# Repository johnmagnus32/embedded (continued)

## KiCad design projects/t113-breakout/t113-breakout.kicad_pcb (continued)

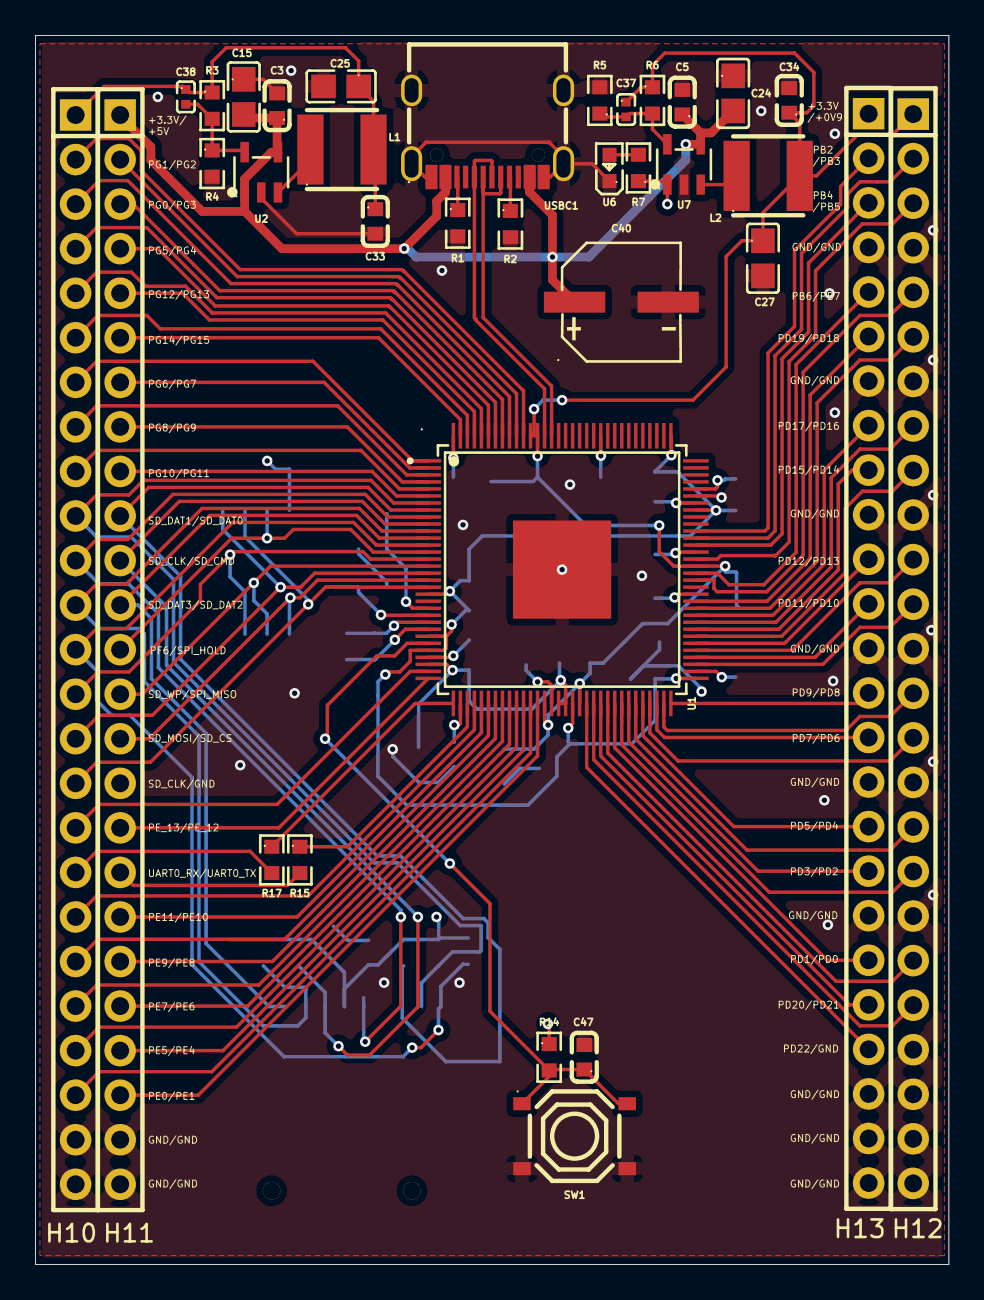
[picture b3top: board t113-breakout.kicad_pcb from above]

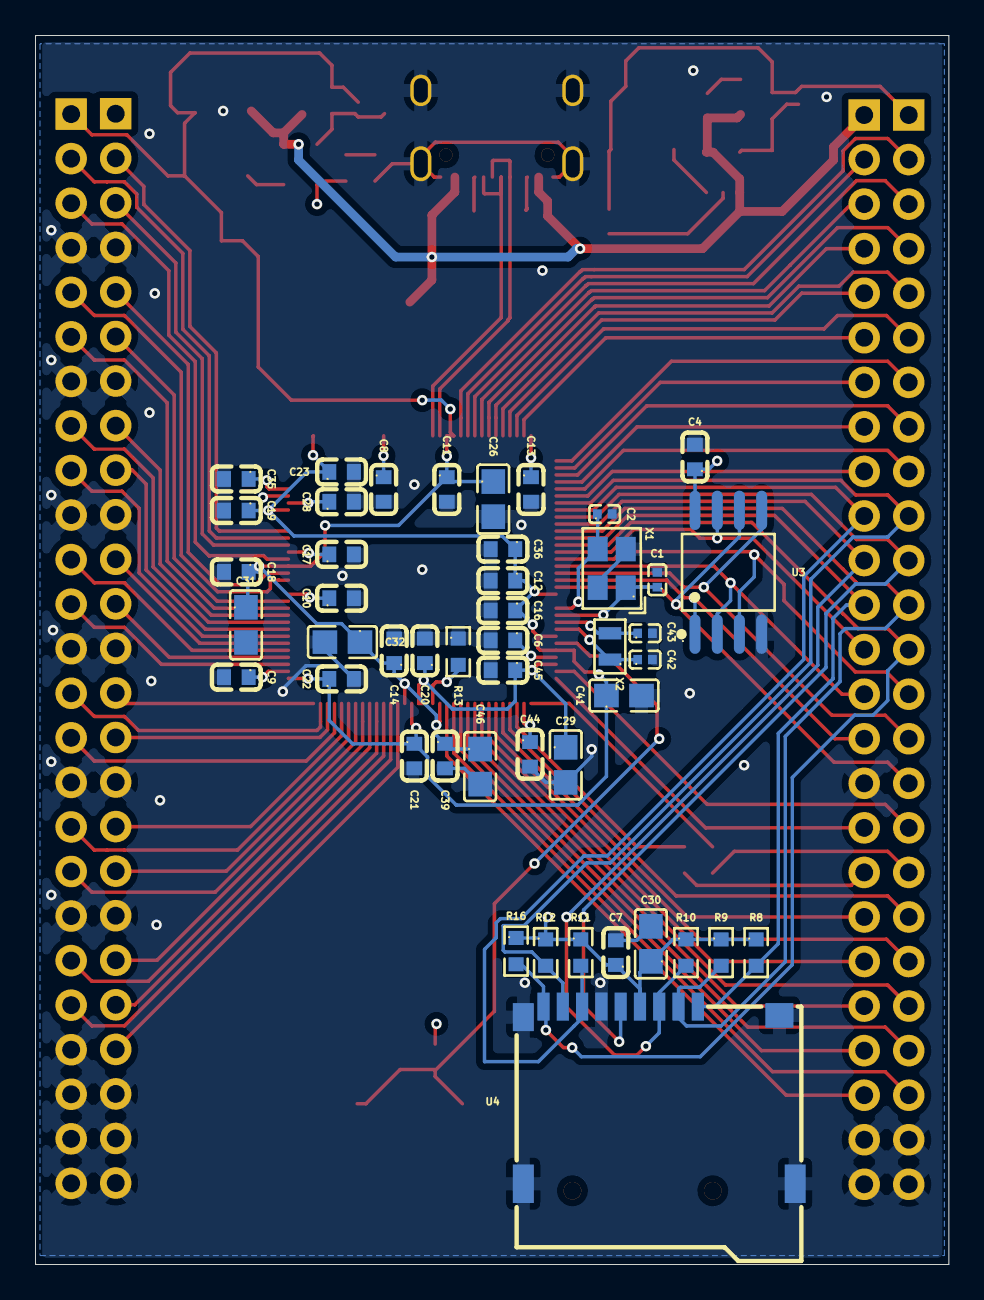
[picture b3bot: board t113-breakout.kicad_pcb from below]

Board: 4 copper layers, 52.1 x 70.1 mm, 80 parts (46 on the bottom side), 97 nets.

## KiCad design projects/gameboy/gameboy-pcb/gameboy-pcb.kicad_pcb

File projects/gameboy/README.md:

# Gameboy — STM32F411RE Jump Game

A side-scrolling jump game running on the STM32F411RE with an ILI9341 display, I2S audio, and button input.

## Pin Assignments (Nucleo-F411RE)

| Pin | Function | Peripheral | Notes |
|-----|----------|-----------|-------|
| PA4 | CS | SPI1 / ILI9341 Display | |
| PA5 | SCK | SPI1 / ILI9341 Display | |
| PA6 | MISO | SPI1 / ILI9341 Display | |
| PA7 | MOSI | SPI1 / ILI9341 Display | |
| PA9 | TX | USART1 (Debug UART) | |
| PA10 | RX | USART1 (Flash upload) | |
| PB0 | CS | W25Q128 Flash | |
| PB5 | DC | ILI9341 Display | |
| PC0 | Button A | Jump | |
| PC1 | Button B | SFX | |
| PC2 | Button Left | — | |
| PC3 | Button Right | — | |
| PC4 | Button Up | — | |
| PC5 | Button Down | — | |
| PC6 | Button Start | — | |
| PC7 | Button Select | — | |
| PB12 | WS (LRCK) | I2S2 (Audio) | |
| PB13 | SCK | I2S2 (Audio) | |
| PB15 | SD | I2S2 (Audio) | |
| PC10 | SCK | SPI3 (Flash) | Morpho header only |
| PC11 | MISO | SPI3 (Flash) | Morpho header only |
| PC12 | MOSI | SPI3 (Flash) | Morpho header only |

**Avoided pins:** PB8/PB9 have I2C pull-ups, PB12 is I2S2_WS on the Nucleo board — not suitable for pull-down buttons.

## ILI9341 Display Wiring

| Display Pin | Connect To |
|-------------|-----------|
| VIN | 5V |
| GND | GND |
| CS | PA4 |
| RESET | 3.3V (tied high) |
| DC | PB5 |
| MOSI (SDA) | PA7 |
| SCK | PA5 |
| LED (LITE) | 3.3V |
| MISO | PA6 |

**Important:** Solder bridge IM1, IM2, IM3 on the back of the display breakout for SPI mode. IM0 stays open.

## Buttons

Buttons connect between the GPIO pin and **3.3V**. Internal pull-down is enabled; rising edge (press down) triggers the interrupt.

| Button | Pin | Function |
|--------|-----|----------|
| A | PC0 | Jump |
| B | PC1 | SFX |
| Left | PC2 | — |
| Right | PC3 | — |
| Up | PC4 | — |
| Down | PC5 | — |
| Start | PC6 | — |
| Select | PC7 | — |

## UART Debug

115200 baud on PA9 (USART1 TX). Connect to a USB-UART adapter's RX pin.

## SPI Clock

SPI1 runs at 8 MHz (APB2 16 MHz / 2 prescaler). ILI9341 max is 10 MHz.

## Building

```bash
make
```

## Flashing (via ST-Link V2 + OpenOCD)

```bash
openocd -f interface/stlink-v2.cfg -f target/stm32f4x.cfg \
  -c "program build/gameboy.elf verify reset exit"
```

## Running in Simulator

```bash
cd ../../sim/mcu
./sim ../../projects/gameboy/build/gameboy.elf ../../projects/gameboy/build/songs.bin
```

Open http://localhost:3000 in a browser.

## Audio

Background music streams from the W25Q128 external flash over SPI3. The jump sound effect is synthesized in firmware.

### Converting audio

Place a WAV file at `assets/music.wav` and run:

```bash
make audio    # → build/songs.bin (8-bit unsigned PCM, 22050 Hz mono)
```

### Programming audio to flash

The firmware includes an upload mode triggered over UART. Requires `pyserial`:

```bash
pip install pyserial
python3 tools/flash_upload.py /dev/ttyUSB0 build/songs.bin
```

This takes ~5 minutes at 115200 baud for a 2.6MB file. The tool:
1. Sends `FLASH\n` to trigger upload mode
2. Firmware stops audio and responds `READY\n`
3. Tool sends 4-byte size + data in 256-byte pages
4. Firmware erases sectors and programs pages
5. Firmware reboots when done

### W25Q128 Flash Wiring

| Flash Pin | Connect To |
|-----------|-----------|
| CLK | PC10 (SPI3 SCK) |
| DI (MOSI) | PC12 (SPI3 MOSI) |
| DO (MISO) | PC11 (SPI3 MISO) |
| /CS | PB0 |
| VCC | 3.3V |
| /HOLD | 3.3V |
| /WP | 3.3V |
| GND | GND |

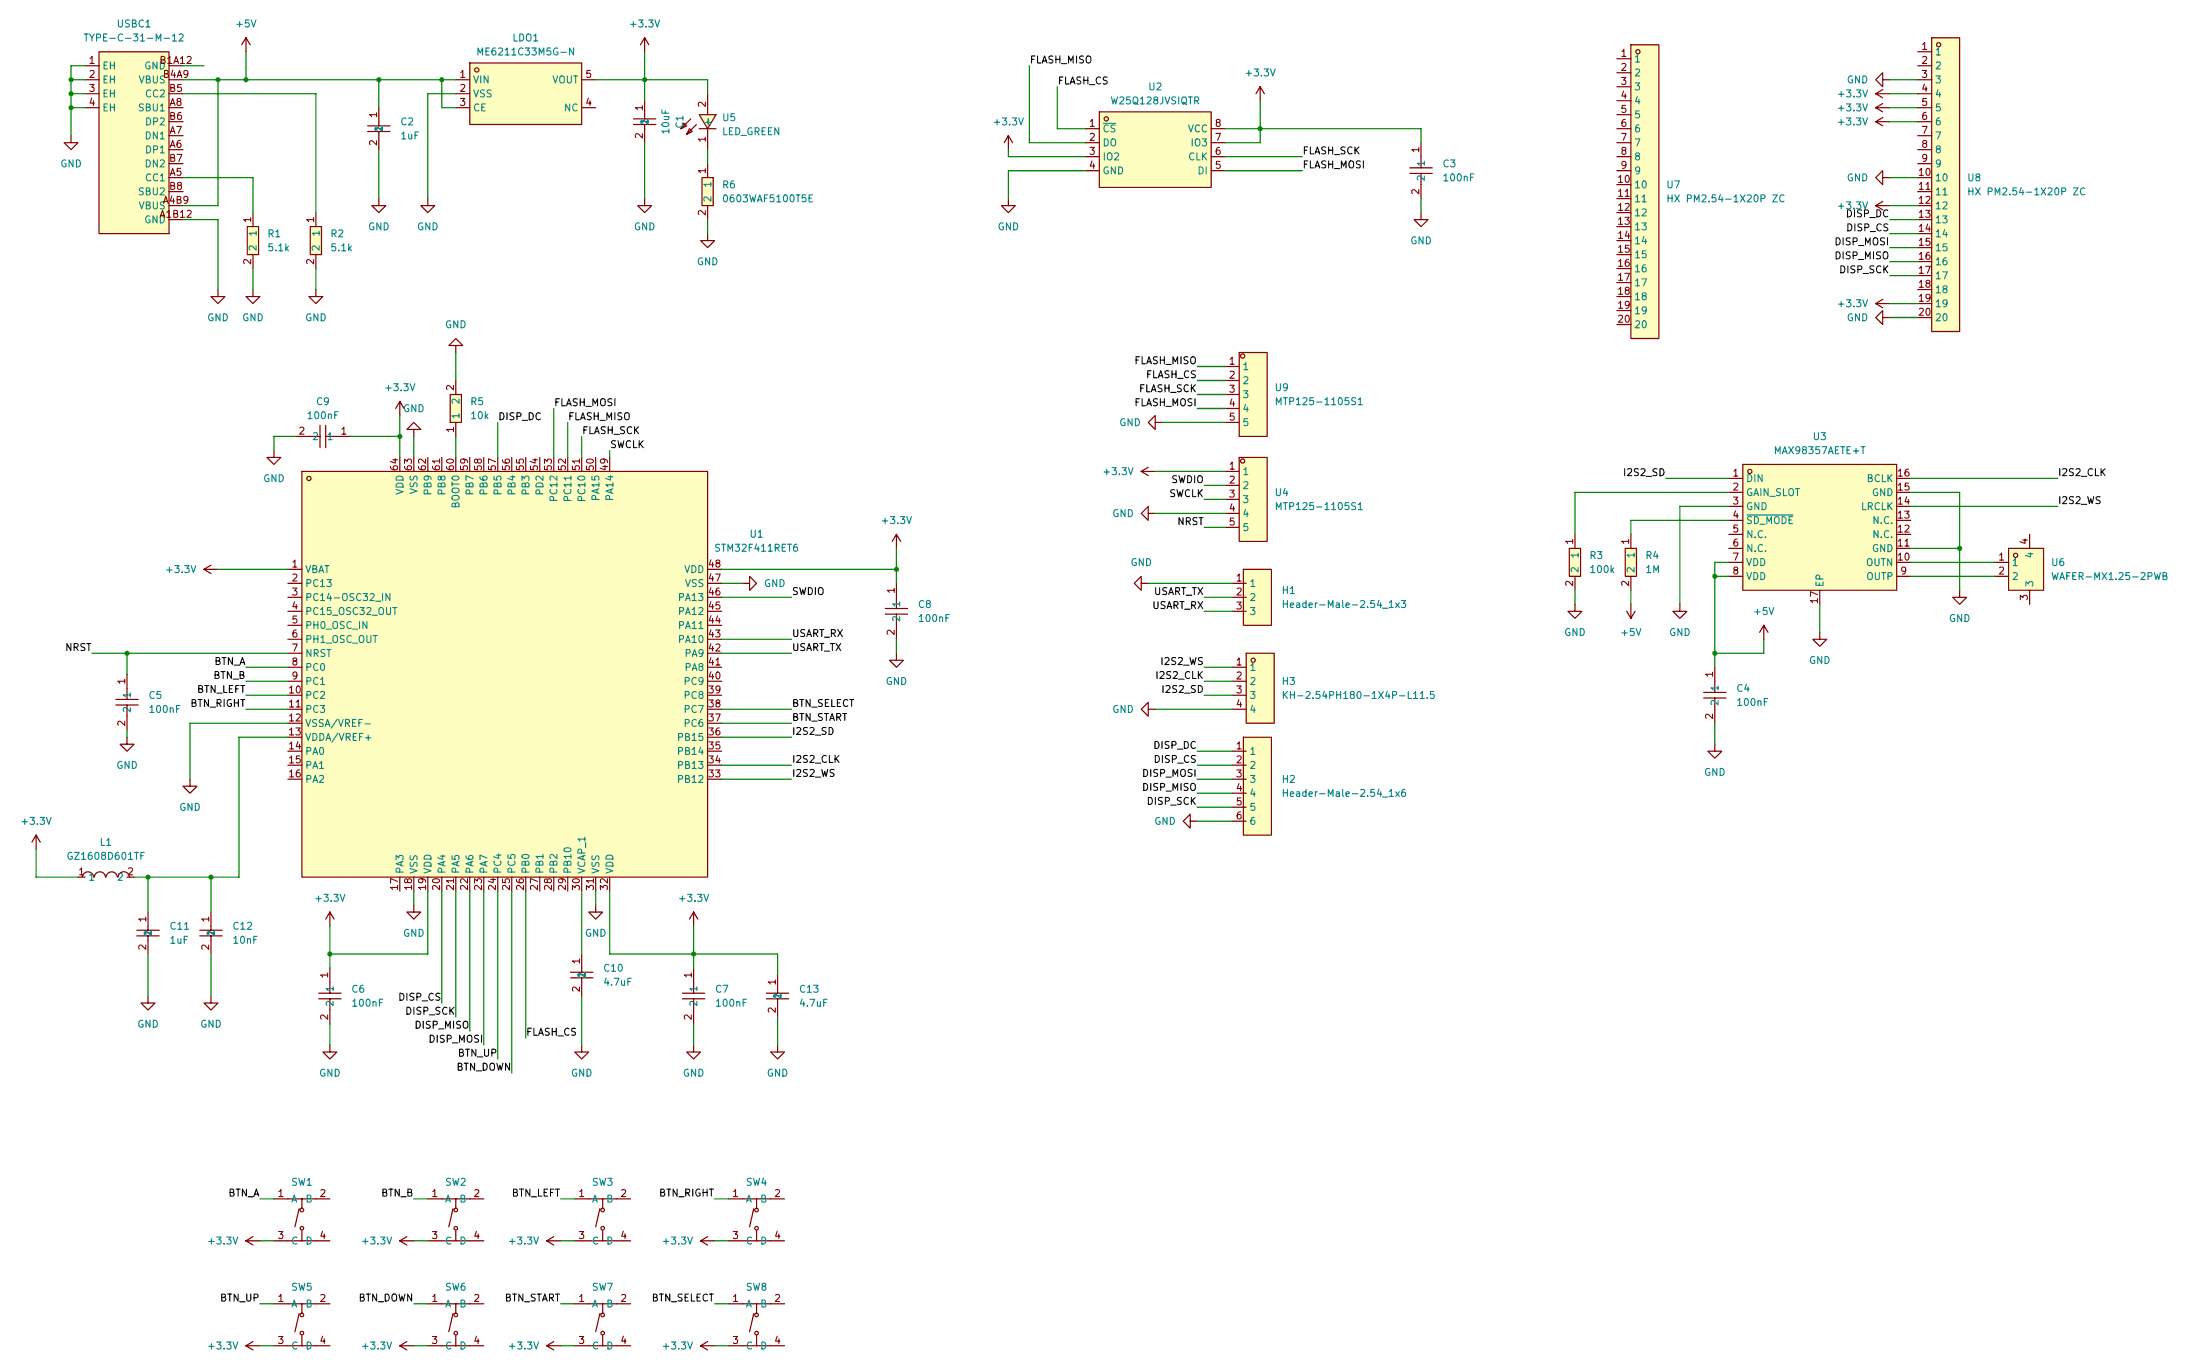
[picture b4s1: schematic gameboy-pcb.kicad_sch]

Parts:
C1: 10uF; C0805; MPN CL21A106KPFNNNE; LCSC Part C17024
C2, C11: 1uF; C0603; MPN CC0603KRX5R7BB105; LCSC Part C106215
C3, C4, C5, C6, C7, C8, C9: 100nF; C0603; MPN CC0603KRX7R9BB104; LCSC Part C14663
C10, C13: 4.7uF; C0603; MPN CC0603KRX5R6BB475; LCSC Part C109456
C12: 10nF; C0603; MPN CC0603KRX7R9BB103; LCSC Part C100042
H1: Header-Male-2.54_1x3; HDR-TH_3P-P2.54-V-M-1; MPN 2.54-1*3P针; LCSC Part C49257
H2: Header-Male-2.54_1x6; HDR-TH_6P-P2.54-V-M-1; MPN 2.54-1x6P直针; LCSC Part C37208
H3: KH-2.54PH180-1X4P-L11.5; HDR-TH_4P-P2.54-V-M; MPN KH-2.54PH180-1X4P-L11.5; LCSC Part C2905435
L1: GZ1608D601TF; L0603; MPN GZ1608D601TF; LCSC Part C1002
LDO1: ME6211C33M5G-N; SOT-23-5_L3.0-W1.7-P0.95-LS2.8-BL; MPN ME6211C33M5G-N; LCSC Part C82942
R1, R2: 5.1k; R0603; MPN RC0603FR-075K1L; LCSC Part C105580
R3: 100k; R0603; MPN RC0603FR-07100KL; LCSC Part C14675
R4: 1M; R0603; MPN RC0603FR-071ML; LCSC Part C105578
R5: 10k; R0603; MPN RC0603JR-0710KL; LCSC Part C99198
R6: 0603WAF5100T5E; R0603; MPN 0603WAF5100T5E; LCSC Part C23193
SW1, SW2, SW3, SW4, SW5, SW6, SW7, SW8: SW-SMD_4P-L5.1-W5.1-P3.70-LS6.5-TL_H1.5; MPN TS-1187A-B-A-B; LCSC Part C318884
U1: STM32F411RET6; LQFP-64_L10.0-W10.0-P0.50-LS12.0-BL; MPN STM32F411RET6; LCSC Part C94355
U2: W25Q128JVSIQTR; SOIC-8_L5.3-W5.3-P1.27-LS8.0-BL; MPN W25Q128JVSIQ; LCSC Part C97521
U3: MAX98357AETE+T; TQFN-16_L3.0-W3.0-P0.50-BL-EP1.5; MPN MAX98357AETE+T; LCSC Part C910544
U4, U9: MTP125-1105S1; HDR-TH_5P-P2.54-V-M; MPN MTP125-1105S1; LCSC Part C358687
U5: LED_GREEN; LED0603-RD; MPN 19-213SYGC/S530-E2/5T; LCSC Part C2986027
U6: WAFER-MX1.25-2PWB; CONN-SMD_2P-P1.25_XUNPU_WAFER-MX1.25-2PWB; MPN WAFER-MX1.25-2PWB; LCSC Part C3029359
U7, U8: HX PM2.54-1X20P ZC; HDR-TH_20P-P2.54-V-F; MPN HX PM2.54-1x20P ZC; LCSC Part C41417332
USBC1: TYPE-C-31-M-12; USB-C_SMD-TYPE-C-31-M-12_1; MPN TYPE-C-31-M-12; LCSC Part C165948

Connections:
+3.3V: C1.1, C3.1, C6.1, C7.1, C8.1, C9.1, C13.1, L1.1, LDO1.5 (VOUT), SW1.3 (C), SW2.3 (C), SW3.3 (C), SW4.3 (C), SW5.3 (C), SW6.3 (C), SW7.3 (C), SW8.3 (C), U1.1 (VBAT), U1.19 (VDD), U1.32 (VDD), U1.48 (VDD), U1.64 (VDD), U2.3 (IO2), U2.7 (IO3), U2.8 (VCC), U4.1, U5.2 (+), U8.4, U8.5, U8.6, U8.12, U8.19
+5V: C2.1, C4.1, LDO1.1 (VIN), LDO1.3 (CE), R4.2, U3.7 (VDD), U3.8 (VDD), USBC1.A4B9 (VBUS), USBC1.B4A9 (VBUS)
/BTN_A: SW1.1 (A), U1.8 (PC0)
/BTN_B: SW2.1 (A), U1.9 (PC1)
/BTN_DOWN: SW6.1 (A), U1.25 (PC5)
/BTN_LEFT: SW3.1 (A), U1.10 (PC2)
/BTN_RIGHT: SW4.1 (A), U1.11 (PC3)
/BTN_SELECT: SW8.1 (A), U1.38 (PC7)
/BTN_START: SW7.1 (A), U1.37 (PC6)
/BTN_UP: SW5.1 (A), U1.24 (PC4)
/DISP_CS: H2.2, U1.20 (PA4), U8.14
/DISP_DC: H2.1, U1.57 (PB5), U8.13
/DISP_MISO: H2.4, U1.22 (PA6), U8.16
/DISP_MOSI: H2.3, U1.23 (PA7), U8.15
/DISP_SCK: H2.5, U1.21 (PA5), U8.17
/FLASH_CS: U1.26 (PB0), U2.1 (~CS), U9.2
/FLASH_MISO: U1.52 (PC11), U2.2 (DO), U9.1
/FLASH_MOSI: U1.53 (PC12), U2.5 (DI), U9.4
/FLASH_SCK: U1.51 (PC10), U2.6 (CLK), U9.3
/I2S2_CLK: H3.2, U1.34 (PB13), U3.16 (BCLK)
/I2S2_SD: H3.3, U1.36 (PB15), U3.1 (DIN)
/I2S2_WS: H3.1, U1.33 (PB12), U3.14 (LRCLK)
/NRST: C5.1, U1.7 (NRST), U4.5
/SWCLK: U1.49 (PA14), U4.3
/SWDIO: U1.46 (PA13), U4.2
/USART_RX: H1.3, U1.43 (PA10)
/USART_TX: H1.2, U1.42 (PA9)
GND: C1.2, C2.2, C3.2, C4.2, C5.2, C6.2, C7.2, C8.2, C9.2, C10.2, C11.2, C12.2, C13.2, H1.1, H2.6, H3.4, LDO1.2 (VSS), R1.2, R2.2, R3.2, R5.2, R6.2, U1.12 (VSSA/VREF-), U1.18 (VSS), U1.31 (VSS), U1.47 (VSS), U1.63 (VSS), U2.4 (GND), U3.3 (GND), U3.11 (GND), U3.15 (GND), U3.17 (EP), U4.4, U8.3, U8.10, U8.20, U9.5, USBC1.1 (EH), USBC1.2 (EH), USBC1.3 (EH), USBC1.4 (EH), USBC1.A1B12 (GND)
unnamed: R5.1, U1.60 (BOOT0)
unnamed: C10.1, U1.30 (VCAP_1)
unnamed: C11.1, C12.1, L1.2, U1.13 (VDDA/VREF+)
unnamed: R3.1, U3.2 (GAIN_SLOT)
unnamed: U3.10 (OUTN), U6.1
unnamed: U3.9 (OUTP), U6.2
unnamed: R4.1, U3.4 (~SD_MODE)
unnamed: R6.1, U5.1 (-)
unnamed: R1.1, USBC1.A5 (CC1)
unnamed: R2.1, USBC1.B5 (CC2)

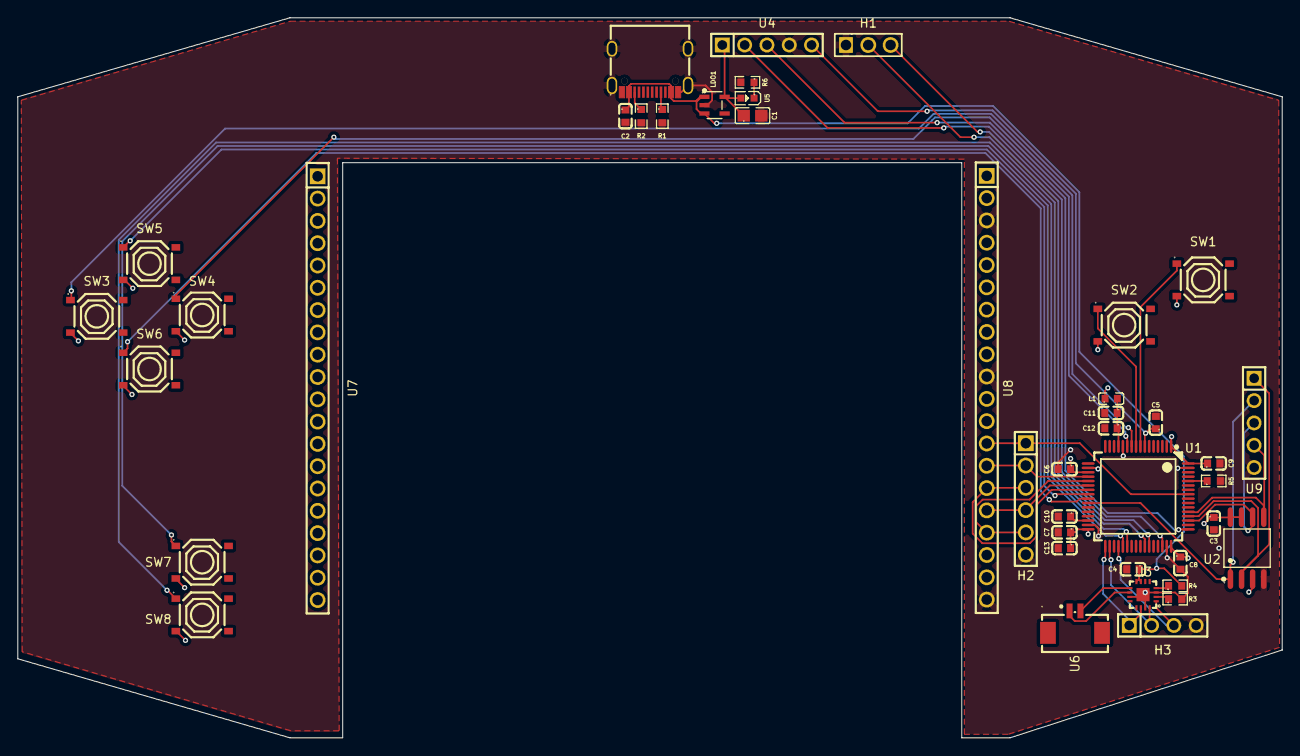
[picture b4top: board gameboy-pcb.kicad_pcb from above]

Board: 4 copper layers, 144.0 x 82.0 mm, 42 parts (0 on the bottom side), 38 nets.

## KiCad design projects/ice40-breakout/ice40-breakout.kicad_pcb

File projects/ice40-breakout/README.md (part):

# Breadboard iCE40UP5K Board (`ice40-breakout`)

**Status:** **Design complete** — schematic (`ice40-breakout.kicad_sch`), PCB
(`ice40-breakout.kicad_pcb`), and JLCPCB production files (`production/`) all live in this
directory. **Not yet fabricated / brought up.** Parts confirmed JLC-sourceable (see `BOM.md`).
**Audience:** Anyone (or a future Claude session) who needs to understand *why* this board exists,
*what it must do*, and *how it was built*. This file is the design rationale + spec; `BOM.md` holds
the as-built bill of materials and the full header pin map.

> **Provenance / how to read the code references.** This board serves a companion firmware project,
> `gameboy-v2`, which at the time of writing lives in `projects/gameboy-v2/` but is **not yet committed
> to git — it is an untracked/uncommitted work tree**. If you are reading this on a clean checkout (or
> a different worktree), those files **will not be present**, and that is expected — do not conclude the
> project "doesn't exist." This document is **self-contained**: every pin assignment, the configuration
> sequence, and the electrical spec are stated inline here and do not require opening any other file to
> trust them. The `projects/gameboy-v2/...` paths are given only so that, *if* you do have that work
> tree, you can cross-check against the source. The facts below are the authority; the file paths are a
> convenience.

> **As-built vs. spec.** Sections 1–3 and 5 were written as *requirements* before layout and remain the
> design rationale. The board has since been **built to this spec** — where a concrete build decision
> differs from or resolves an open question in the text, an **`[AS-BUILT]`** note points at the real
> value. The single authority for the final pinout is **`BOM.md`** (regenerated from
> `production/netlist.ipc`); this document is the *why*, `BOM.md` is the *what*.

---

## 0. In one paragraph

This is a custom breakout board for the **Lattice iCE40UP5K FPGA** (part `iCE40UP5K-SG48I`, the 48-pin
QFN package). In our system the FPGA is used as a graphics coprocessor (a "PPU") and is **configured
by an STM32 microcontroller over SPI at every power-up** — the STM32 streams the FPGA's bitstream in
on boot; there is no configuration flash on the FPGA side. Off-the-shelf iCE40 breakout boards
(iCEBreaker, UPduino) **cannot** be used for this, because they each carry an onboard SPI
configuration flash and a USB programmer wired onto the same SPI bus the STM32 needs to drive —
they contend on that bus and force the FPGA into self-boot ("master") mode. This board therefore
strips all of that out: it exposes just the FPGA, its power, and its config + I/O pins, so an external
STM32 is the sole controller of the configuration bus. Details below.

---

## 1. Why this board exists

### The product: gameboy-v2

`projects/gameboy-v2` is a handheld game console built from **two chips**:

- **STM32F411RE** (ARM Cortex-M4) — runs the game logic, audio, and input. Acts as the "CPU."
- **iCE40UP5K** (Lattice FPGA) — a **Picture Processing Unit (PPU)**. It renders sprites to an
  ILI9341 LCD autonomously. The STM32 sends sprite positions over SPI each frame; the FPGA does all
  pixel work and drives the display.

The defining architectural decision of gameboy-v2: **the STM32 configures the FPGA at every boot.**
The FPGA bitstream is *embedded in the STM32's firmware flash* and streamed into the FPGA over SPI on
power-up. There is **no FPGA-side configuration flash** in the product. (In the firmware this is a
function `fpga_load_bitstream()` that runs first thing in `main()`, before the game starts — the exact
sequence it performs is reproduced in section 2 below, so you do not need the source to follow it.)

Why do it this way? The iCE40 is **SRAM-based**: its logic configuration lives in volatile on-chip
SRAM that is wiped on every power loss. Something must reload it each boot. The gameboy-v2 chooses to
make the STM32 that "something" — one firmware image contains both the CPU program and the FPGA
bitstream, one flash operation programs the whole system, and there is no second flash chip to stock,
place, or program.

### The problem: dev boards don't work this way

The obvious way to prototype is to buy an off-the-shelf iCE40 dev board (iCEBreaker, UPduino) and wire
it to a Nucleo. **This does not faithfully reproduce the gameboy-v2 boot path**, for a concrete
electrical reason:

- Those boards are designed to **self-boot from an onboard SPI config flash** (iCE40 "master mode").
  They also carry an FTDI USB chip that programs that flash.
- Both the flash and the FTDI are wired **onto the FPGA's configuration SPI bus**. The config
  chip-select line (`SPI_SS_B`) is *the same net* as the flash's chip-select.
- If an external STM32 tries to slave-configure the FPGA, it must drive `SPI_SS_B` low — which also
  selects the onboard flash, causing **bus contention** on the shared data line. (This is the same
  reason `iceprog --help` notes that an iCEstick needs its flash chip desoldered for direct SRAM
  programming.)

So on a stock dev board you cannot cleanly let the STM32 own the config bus without physically
removing the flash. That is fragile and not representative.

### What this board is

A **minimal iCE40UP5K breakout with no onboard config flash and no USB programmer** — just the FPGA,
its power, decoupling, and headers. The STM32 is the *only* master of the config bus. This lets us:

1. Run the **exact, unmodified gameboy-v2 firmware** (`fpga_load_bitstream()` and all runtime code)
   on a breadboard, with the STM32 configuring the FPGA at boot — bit-for-bit like the final product.
2. Validate the real boot path, SPI protocol, PPU rendering, and LCD output on real silicon before
   committing to the integrated gameboy-v2 PCB.
3. Iterate on hardware cheaply (a ~15-component 2-layer board) with the risky/expensive integration
   (STM32 + FPGA + flash + LCD + audio on one board) deferred until the fundamentals are proven.

**Non-goal:** This board is *not* meant to self-boot or be programmed over USB. It has no persistence
of its own. If it has no STM32 driving it, it does nothing — exactly like the FPGA in the final
product.

---

## 2. The boot / configuration model (must be reproduced exactly)

The board's whole reason for existing is to reproduce this sequence, so it is spelled out in full here
(you do not need any other file to implement it). This is the **iCE40 SPI-slave configuration**
procedure (Lattice TN1248); the gameboy-v2 firmware implements it in `src/fpga_loader.c` — a function
named `fpga_load_bitstream()` called from `main()` before the game starts — but that file is in the
uncommitted work tree, so the canonical description is the numbered steps below:

```
1. CRESET_B  -> low     Clear configuration SRAM.
2. SPI_SS_B  -> low     Select SPI SLAVE config mode (this level is sampled when CRESET releases).
3. (hold ~1 us)
4. CRESET_B  -> high    Release reset. FPGA clears CRAM, then waits for the bitstream.
5. (wait ~1200 us)      Give the chip time to clear config memory before clocking data.
6. Clock the bitstream on MOSI, SPI mode 0 (CPOL=0, CPHA=0), MSB first.
7. Send >=49 trailing dummy clocks (firmware sends 7 bytes = 56 clocks) to finish wake-up.
8. SPI_SS_B  -> high    Release select. FPGA transitions to user mode.
9. CDONE goes high      Success indicator (read by the STM32). If it stays low, config failed.
```

**Boot-mode selection is a single strap:** the level on `SPI_SS_B` at the instant `CRESET_B` is
released decides master vs slave:
- `SPI_SS_B` sampled **low**  -> **slave** mode (wait to be fed) — what gameboy-v2 forces.
- `SPI_SS_B` sampled **high** -> **master** mode (self-load from external flash) — what dev boards do.

On this board there is no flash on the `SPI_SS_B` net, so the STM32 can drive it low at reset to select
slave mode with nothing to contend against. (This is the electrical fix for the dev-board problem in
section 1.)

> Hardware-spec values (min CRESET low pulse, the wait-after-CRESET, exact dummy-clock count, whether
> CDONE needs an external pull-up) are being cross-checked against the Lattice datasheet / TN1248 and
> will be filled into section 5. The firmware currently uses 1 us / 1200 us / 56 clocks, which has
> worked in simulation; confirm against silicon.

---

## 3. Interfaces the board must expose

All signals are **3.3 V** on both the STM32F411 and the iCE40UP5K I/O banks, so **no level shifters
are required**. The pin assignments below are authoritative *as stated here*. They are transcribed
from the gameboy-v2 firmware's device tree (`board.dts`) and the FPGA constraints file
(`fpga/icebreaker.pcf`) — but those files are part of the uncommitted `projects/gameboy-v2/` work tree
(see Provenance note at top), so treat the tables here as the source of record and cross-check the
files only if you have them.

### 3a. Configuration bus (STM32 SPI3 + GPIO -> FPGA config pins)

Used only at boot, by `fpga_load_bitstream()`. This is the interface that stock dev boards cannot
expose cleanly.

| Role | STM32 pin | STM32 function | iCE40 config pin |
|------|-----------|----------------|------------------|
| Config SPI clock | PC10 | SPI3_SCK (AF6) | SPI_SCK |
| Config SPI data  | PC12 | SPI3_MOSI (AF6) | SPI_SI (a.k.a. SDI) |
| Config select    | PB6  | GPIO out       | SPI_SS_B |
| Config reset     | PB1  | GPIO out       | CRESET_B |
| Config done      | PB2  | GPIO in        | CDONE |

Notes:
- SPI3_MISO (PC11) is wired in `board.dts` but configuration is write-only from the STM32's side; the
  FPGA's `SPI_SO` is not needed for slave config. (Confirm whether `SPI_SO` should be left floating or
  pulled — see section 5.)
- On the real gameboy-v2 this same SPI3 bus is also shared with a W25Q128 flash (for audio). **This
  breadboard board does not need that flash** — it is only for the config path. Audio flash can be
  added later or omitted during bring-up.

### 3b. Runtime game-data bus (STM32 SPI1 -> FPGA) — the PPU command channel

Used every frame after boot. One-way (STM32 -> FPGA), so no MISO. CS is bit-banged as a plain GPIO in
`projects/gameboy-v2/src/ppu.c` (not hardware NSS).

| Role | STM32 pin | STM32 function | iCE40 pin (from .pcf) |
|------|-----------|----------------|------------------------|
| SPI clock | PA5 | SPI1_SCK (AF5) | 4  (net `SPI_CLK`) |
| SPI MOSI  | PA7 | SPI1_MOSI (AF5) | 2  (net `SPI_MOSI`) |
| SPI CS    | PA4 | GPIO out       | 47 (net `SPI_CS`) |

### 3c. Runtime display bus (FPGA -> ILI9341, 8-bit parallel / Intel 8080)

The FPGA drives the LCD directly. This is a **parallel 8080 bus**, *not* SPI — most cheap ILI9341
breakouts are SPI-only, so a parallel-capable module is required.

| Signal | iCE40 pin (from .pcf) |
|--------|------------------------|
| LCD_D0..D3 | 43, 38, 34, 31 |
| LCD_D4..D7 | 28, 27, 26, 25 |
| LCD_WR (write strobe) | 21 |
| LCD_DC (data/command) | 20 |
| LCD_CS (chip select)  | 19 |

Display wiring gotchas (the FPGA only ever *writes*):
- Tie the display's **RD** high (3.3 V) — the FPGA never reads.
- Tie/drive **RESET** high (3.3 V, or via RC, or a spare GPIO).
- Wire the backlight per the module (usually 3.3 V through a resistor).

> The pin numbers above are the iCE40 package ball/pad numbers as used in the current `.pcf`, which
> targets the iCEBreaker's PMOD layout. **When laying out a custom board these can be reassigned to
> whatever routes cleanly** — but if they change, `icebreaker.pcf` must be updated to match, and the
> bitstream re-synthesized. Keep a board-specific `.pcf` alongside the design.
>
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
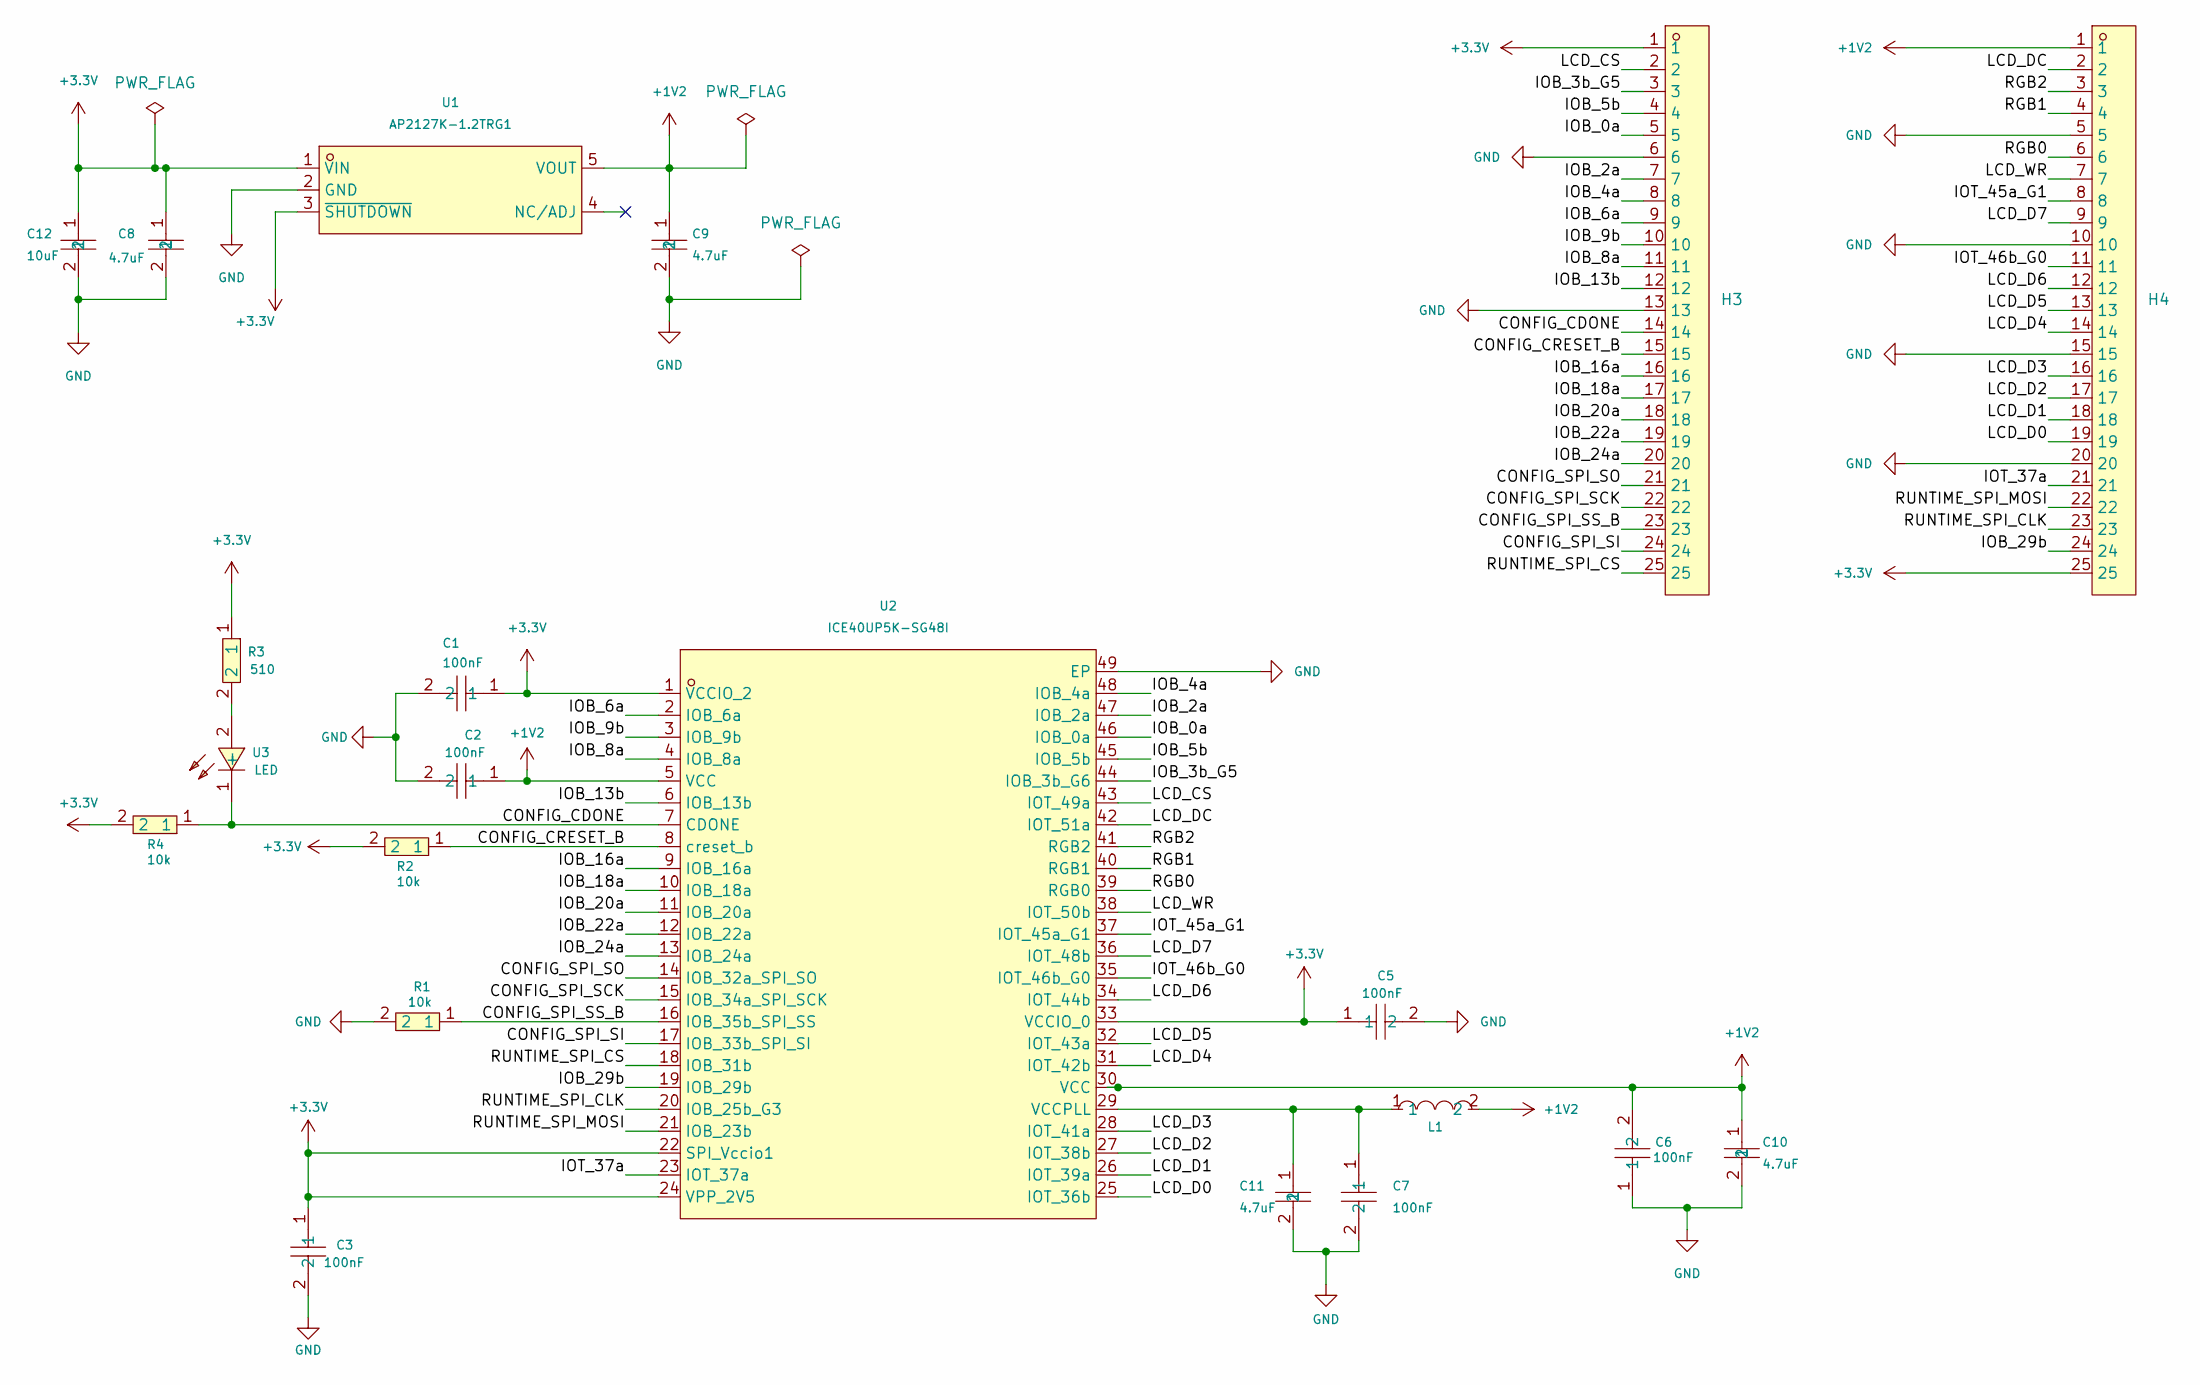
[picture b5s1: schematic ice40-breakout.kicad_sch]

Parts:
C1, C2, C3, C5, C6, C7: 100nF; C0603; MPN CC0603KRX7R9BB104; LCSC Part C14663
C8, C9, C10, C11: 4.7uF; C0603; MPN CC0603KRX5R6BB475; LCSC Part C109456
C12: 10uF; C0805; MPN CL21A106KOQNNNE; LCSC Part C1713
H3, H4: 2044-1X25G00SA; HDR-TH_25P-P2.54-V-F_2044-1X25G00SA; MPN 2044-1X25G00SA; LCSC Part C49569761
L1: GZ1608D601TF; L0603; MPN GZ1608D601TF; LCSC Part C1002
R1, R2, R4: 10k; R0603; MPN RC0603JR-0710KL; LCSC Part C99198
R3: 510; R0603; MPN 0603WAF5100T5E; LCSC Part C23193
U1: AP2127K-1.2TRG1; SOT-23-5_L3.0-W1.7-P0.95-LS2.8-BR; MPN AP2127K-1.2TRG1; LCSC Part C151376
U2: ICE40UP5K-SG48I; QFN-48_L7.0-W7.0-P0.50-TL-EP5.4-1; MPN ICE40UP5K-SG48I; LCSC Part C2678152
U3: LED; LED0603-RD; MPN 19-213SYGC/S530-E2/5T; LCSC Part C2986027

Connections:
+1V2: C2.1, C6.2, C9.1, C10.1, H4.1, L1.2, U1.5 (VOUT), U2.5 (VCC), U2.30 (VCC)
+3.3V: C1.1, C3.1, C5.1, C8.1, C12.1, H3.1, H4.25, R2.2, R3.1, R4.2, U1.1 (VIN), U1.3 (~SHUTDOWN), U2.1 (VCCIO_2), U2.22 (SPI_Vccio1), U2.24 (VPP_2V5), U2.33 (VCCIO_0)
/CONFIG_CDONE: H3.14, R4.1, U2.7 (CDONE), U3.1 (-)
/CONFIG_CRESET_B: H3.15, R2.1, U2.8 (creset_b)
/CONFIG_SPI_SCK: H3.22, U2.15 (IOB_34a_SPI_SCK)
/CONFIG_SPI_SI: H3.24, U2.17 (IOB_33b_SPI_SI)
/CONFIG_SPI_SO: H3.21, U2.14 (IOB_32a_SPI_SO)
/CONFIG_SPI_SS_B: H3.23, R1.1, U2.16 (IOB_35b_SPI_SS)
/IOB_0a: H3.5, U2.46 (IOB_0a)
/IOB_2a: H3.7, U2.47 (IOB_2a)
/IOB_3b_G5: H3.3, U2.44 (IOB_3b_G6)
/IOB_4a: H3.8, U2.48 (IOB_4a)
/IOB_5b: H3.4, U2.45 (IOB_5b)
/IOB_6a: H3.9, U2.2 (IOB_6a)
/IOB_8a: H3.11, U2.4 (IOB_8a)
/IOB_9b: H3.10, U2.3 (IOB_9b)
/IOB_13b: H3.12, U2.6 (IOB_13b)
/IOB_16a: H3.16, U2.9 (IOB_16a)
/IOB_18a: H3.17, U2.10 (IOB_18a)
/IOB_20a: H3.18, U2.11 (IOB_20a)
/IOB_22a: H3.19, U2.12 (IOB_22a)
/IOB_24a: H3.20, U2.13 (IOB_24a)
/IOB_29b: H4.24, U2.19 (IOB_29b)
/IOT_37a: H4.21, U2.23 (IOT_37a)
/IOT_45a_G1: H4.8, U2.37 (IOT_45a_G1)
/IOT_46b_G0: H4.11, U2.35 (IOT_46b_G0)
/LCD_CS: H3.2, U2.43 (IOT_49a)
/LCD_D0: H4.19, U2.25 (IOT_36b)
/LCD_D1: H4.18, U2.26 (IOT_39a)
/LCD_D2: H4.17, U2.27 (IOT_38b)
/LCD_D3: H4.16, U2.28 (IOT_41a)
/LCD_D4: H4.14, U2.31 (IOT_42b)
/LCD_D5: H4.13, U2.32 (IOT_43a)
/LCD_D6: H4.12, U2.34 (IOT_44b)
/LCD_D7: H4.9, U2.36 (IOT_48b)
/LCD_DC: H4.2, U2.42 (IOT_51a)
/LCD_WR: H4.7, U2.38 (IOT_50b)
/RGB0: H4.6, U2.39 (RGB0)
/RGB1: H4.4, U2.40 (RGB1)
/RGB2: H4.3, U2.41 (RGB2)
/RUNTIME_SPI_CLK: H4.23, U2.20 (IOB_25b_G3)
/RUNTIME_SPI_CS: H3.25, U2.18 (IOB_31b)
/RUNTIME_SPI_MOSI: H4.22, U2.21 (IOB_23b)
GND: C1.2, C2.2, C3.2, C5.2, C6.1, C7.2, C8.2, C9.2, C10.2, C11.2, C12.2, H3.6, H3.13, H4.5, H4.10, H4.15, H4.20, R1.2, U1.2 (GND), U2.49 (EP)
unnamed: C7.1, C11.1, L1.1, U2.29 (VCCPLL)
unnamed: R3.2, U3.2 (+)

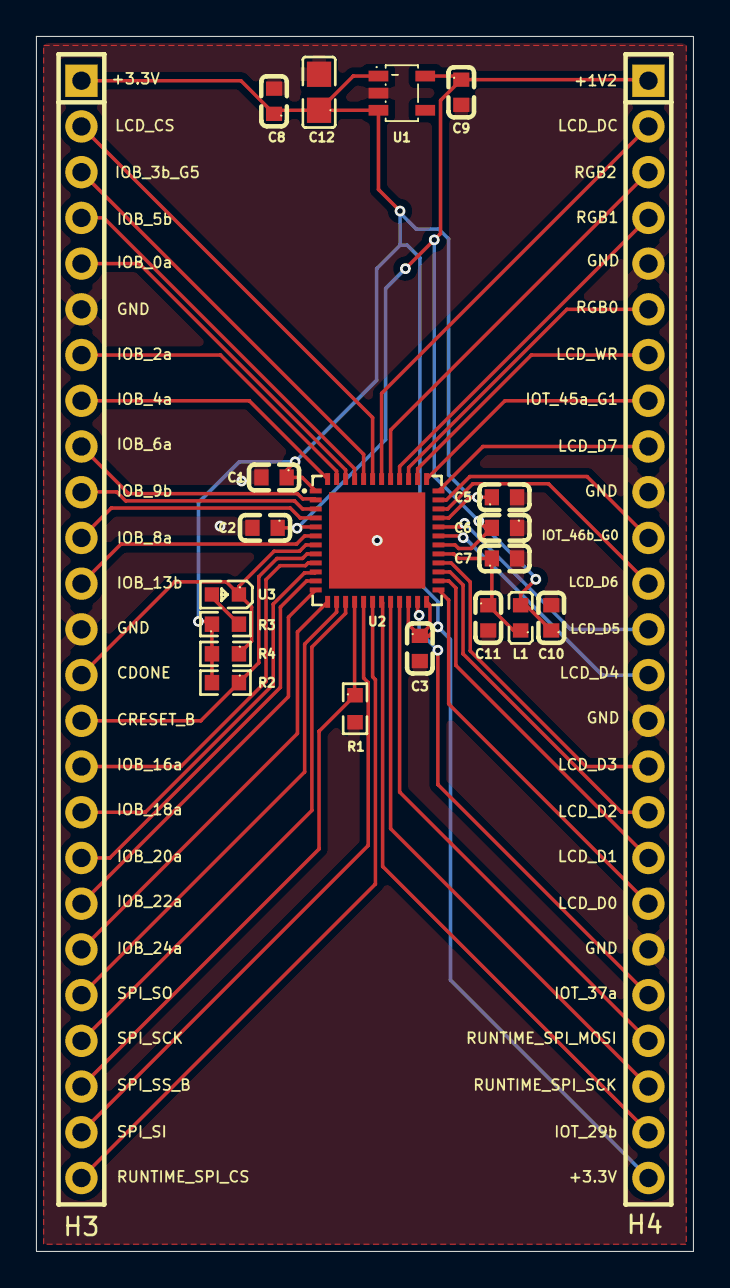
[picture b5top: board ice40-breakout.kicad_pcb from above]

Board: 2 copper layers, 36.5 x 67.5 mm, 21 parts (0 on the bottom side), 46 nets.

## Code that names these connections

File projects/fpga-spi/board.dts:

/*
 * fpga-spi board device tree — STM32F411RE (Nucleo) + ice40-breakout.
 *
 * Two SPI buses to the FPGA:
 *   spi3 (config) — streams the bitstream in at boot via the iCE40 loader
 *                   driver. SCK=PC10, MOSI=PC12; CRESET/CDONE/SS on PB1/PB2/PB6.
 *                   Runs at BR=/2 (~8 MHz off 16 MHz HSI), inside the iCE40
 *                   1-25 MHz slave-config window.
 *   spi1 (runtime)— the LED command channel to the *configured* FPGA. The STM32
 *                   is master; one command byte per CS frame sets LED0/LED1.
 *                   SCK=PA5, MOSI=PA7, hardware CS=PA4. Runs SLOW (br=5 → /64 →
 *                   ~250 kHz): the FPGA slave oversamples with a 12 MHz clock +
 *                   3-stage synchronizer and can't track multi-MHz SCK.
 *
 * Runtime pin map (ice40-breakout BOM.md as-built):
 *   SPI1 SCK  = PA5 (AF5) -> H4-23 -> iCE40 pin 20 (RUNTIME_SPI_CLK)
 *   SPI1 MOSI = PA7 (AF5) -> H4-22 -> iCE40 pin 21 (RUNTIME_SPI_MOSI)
 *   SPI1 CS   = PA4 (GPIO)-> H3-25 -> iCE40 pin 18 (RUNTIME_SPI_CS)
 *   LED0 fb   = PC0 (in)  <- H3-8  <- iCE40 pin 48 (LED0, IOB_4A)
 *   LED1 fb   = PC1 (in)  <- H3-9  <- iCE40 pin 2  (LED1, IOB_6A)
 * PC0/PC1 are read as plain GPIO inputs by the app (not DT device nodes).
 */
/ {
    compatible = "st,nucleo-f411re";
    model = "STM32F411RE Nucleo + ice40-breakout (fpga-spi)";

    clocks {
        hsi: hsi {
            compatible = "fixed-clock";
            clock-frequency = <16000000>;
        };
    };

    soc {
        compatible = "st,stm32f411";

        rcc: rcc@40023800 {
            compatible = "st,stm32-rcc";
            reg = <0x40023800>;
        };

        gpioa: gpio@40020000 {
            compatible = "st,stm32-gpio";
            reg = <0x40020000>;
            clocks = <&rcc 0 0>;
        };

        gpiob: gpio@40020400 {
            compatible = "st,stm32-gpio";
            reg = <0x40020400>;
            clocks = <&rcc 0 1>;
        };

        gpioc: gpio@40020800 {
            compatible = "st,stm32-gpio";
            reg = <0x40020800>;
            clocks = <&rcc 0 2>;
        };

        usart2: serial@40004400 {
            compatible = "st,stm32-usart";
            reg = <0x40004400>;
            clocks = <&rcc 1 17>;   /* APB1 bit 17 = USART2EN */
            tx-pin = <2>;
            tx-af = <7>;
            tx-port = <&gpioa>;
            rx-pin = <3>;
            rx-af = <7>;
            rx-port = <&gpioa>;
            baudrate = <115200>;
            irq = <38>;             /* USART2 global interrupt */
            status = "okay";
        };

        /* SPI1: runtime LED command bus. SLOW (br=5 → fPCLK/64 → ~250 kHz) so
         * the FPGA's oversampled SPI slave can track it. Hardware CS = PA4. */
        spi1: spi@40013000 {
            compatible = "st,stm32-spi";
            reg = <0x40013000>;
            clocks = <&rcc 2 12>;   /* APB2 bit 12 = SPI1EN */
            br = <5>;               /* fPCLK/64 */
            sck-port = <&gpioa>;
            sck-pin = <5>;
            sck-af = <5>;
            miso-port = <&gpioa>;
            miso-pin = <6>;
            miso-af = <5>;
            mosi-port = <&gpioa>;
            mosi-pin = <7>;
            mosi-af = <5>;
            cs-port = <&gpioa>;
            cs-pin = <4>;
            status = "okay";
        };

        /* SPI3: iCE40 bitstream configuration bus (BR defaults to /2). */
        spi3: spi@40003C00 {
            compatible = "st,stm32-spi";
            reg = <0x40003C00>;
            clocks = <&rcc 1 15>;   /* APB1 bit 15 = SPI3EN */
            sck-port = <&gpioc>;
            sck-pin = <10>;
            sck-af = <6>;
            miso-port = <&gpioc>;
            miso-pin = <11>;
            miso-af = <6>;
            mosi-port = <&gpioc>;
            mosi-pin = <12>;
            mosi-af = <6>;
            /* No hardware CS — the ice40 loader drives SPI_SS_B (PB6) as GPIO.
             * PB0 is an unused placeholder the SPI driver parks high. */
            cs-port = <&gpiob>;
            cs-pin = <0>;
            status = "okay";

            ice40cfg: ice40-cfg {
                compatible = "lattice,ice40up5k-cfg";
                creset-port = <&gpiob>;
                creset-pin = <1>;
                cdone-port = <&gpiob>;
                cdone-pin = <2>;
                ss-port = <&gpiob>;
                ss-pin = <6>;
                status = "okay";
            };
        };
    };

    chosen {
        console = <&usart2>;
    };
};

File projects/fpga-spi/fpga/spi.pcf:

# Pin constraints for the ice40-breakout board (projects/ice40-breakout).
#
# These are the REAL as-built package pins from
# projects/ice40-breakout/BOM.md — NOT the iCEBreaker/PMOD numbers a stock
# .pcf would use. (fpga-blink learned this the hard way; the stock icebreaker
# .pcf maps signals to the wrong physical pins on this board.)
#
# Runtime SPI command bus (STM32 SPI master -> FPGA slave):
#   SPI_CLK  net RUNTIME_SPI_CLK  = pin 20 -> header H4-23  (STM32 PA5, SPI1_SCK)
#   SPI_MOSI net RUNTIME_SPI_MOSI = pin 21 -> header H4-22  (STM32 PA7, SPI1_MOSI)
#   SPI_CS   net RUNTIME_SPI_CS   = pin 18 -> header H3-25  (STM32 PA4, GPIO)
set_io SPI_CLK  20
set_io SPI_MOSI 21
set_io SPI_CS   18

# LED outputs — each drives an external LED (pin -> ~330R -> LED -> GND) AND
# an STM32 feedback input so the firmware can read its own commands back:
#   LED0 = pin 48 (IOB_4A) -> header H3-8 -> STM32 PC0 (feedback in)
#   LED1 = pin 2  (IOB_6A) -> header H3-9 -> STM32 PC1 (feedback in)
set_io LED0 48
set_io LED1 2

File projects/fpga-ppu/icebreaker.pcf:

# iCEBreaker pin assignments for PPU
# SPI from STM32 (PMOD 1A)
set_io SPI_CLK  4
set_io SPI_MOSI 2
set_io SPI_CS   47

# SPI to ILI9341 (PMOD 1B)
set_io LCD_SCLK 43
set_io LCD_MOSI 38
set_io LCD_CS   34
set_io LCD_DC   31

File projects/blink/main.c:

/*
 * blink.c — Bare-metal LED blink + UART for STM32F411RE Nucleo
 * LD2 = PA5, USART1 TX = PA9, RX = PA10
 */
#include <stdint.h>

/* RCC */
#define RCC_AHB1ENR  (*(volatile uint32_t *)0x40023830)
#define RCC_APB2ENR  (*(volatile uint32_t *)0x40023844)

/* GPIOA */
#define GPIOA_MODER  (*(volatile uint32_t *)0x40020000)
#define GPIOA_AFRH   (*(volatile uint32_t *)0x40020024)
#define GPIOA_ODR    (*(volatile uint32_t *)0x40020014)

/* USART1 (on APB2) */
#define USART1_SR    (*(volatile uint32_t *)0x40011000)
#define USART1_DR    (*(volatile uint32_t *)0x40011004)
#define USART1_BRR   (*(volatile uint32_t *)0x40011008)
#define USART1_CR1   (*(volatile uint32_t *)0x4001100C)

extern uint32_t _stack_top;
void reset_handler(void);

__attribute__((section(".vector_table"), used))
void (* const vectors[])(void) = {
    (void (*)(void))&_stack_top,
    reset_handler,
};

static void delay(volatile uint32_t count)
{
    while (count--) ;
}

static void uart_putc(char c)
{
    while (!(USART1_SR & (1 << 7))) ;
    USART1_DR = c;
}

static void uart_puts(const char *s)
{
    while (*s) uart_putc(*s++);
}

void reset_handler(void)
{
    /* Enable GPIOA + USART1 clocks */
    RCC_AHB1ENR |= (1 << 0);       /* GPIOA */
    RCC_APB2ENR |= (1 << 4);       /* USART1 */
    delay(10);

    /* PA5 = output (LED) */
    GPIOA_MODER &= ~(3 << 10);
    GPIOA_MODER |=  (1 << 10);

    /* PA9 = AF7 (USART1_TX), PA10 = AF7 (USART1_RX) */
    GPIOA_MODER &= ~((3 << 18) | (3 << 20));
    GPIOA_MODER |=  ((2 << 18) | (2 << 20));
    GPIOA_AFRH  &= ~((0xF << 4) | (0xF << 8));
    GPIOA_AFRH  |=  ((7 << 4) | (7 << 8));

    /* USART1: 115200 baud at 16MHz HSI (APB2 = 16MHz) */
    USART1_BRR = 0x008B;
    USART1_CR1 |= (1 << 13);
    delay(10);
    USART1_CR1 |= (1 << 3) | (1 << 2);

    int count = 0;
    while (1) {
        GPIOA_ODR ^= (1 << 5);
        uart_puts("blink ");
        char buf[12];
        int i = 11;
        buf[i] = 0;
        int v = count;
        if (v == 0) { buf[--i] = '0'; }
        else { while (v > 0) { buf[--i] = '0' + (v % 10); v /= 10; } }
        uart_puts(&buf[i]);
        uart_puts("\r\n");
        count++;
        delay(500000);
    }
}

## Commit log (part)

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2026-05-07 feat(gameboy): Add I2S audio output and fix display colors
    Audio:
    - Enable PLLI2S (default N=192, R=2 → 96 MHz I2SCLK)
    - Configure I2S2 pins (PB12/PB13/PB15) as AF5 in early init
    - Fix I2S driver: set Master TX mode, proper prescaler (DIV=68
    for 22 kHz at 96 MHz)
    - Synthesized jump SFX (frequency sweep) replacing silent placeholder
2026-05-07 refactor: Restructure project (os→rtos, sim→sim/mcu) and add features
    Major restructuring:
    - Rename os/ to rtos/ for clarity
    - Move sim to sim/mcu/ to support future sim targets
    - Add FPGA projects (fpga-blink, fpga-ppu)
    Debugger:
    - GDB RSP stub replacing custom debug protocol
2026-05-07 refactor(rtos): Add device init priorities to fix init ordering
    Problem:
    The ILI9341 display driver was being initialized before the SPI1 bus
    driver due to arbitrary linker section ordering. This caused the
    display init to send commands over an unconfigured SPI bus, requiring
    a 40-line block of raw register writes in main.c to manually set up
    clocks, GPIO pins, and peripherals before device_init_all() ran.
2026-05-12 feat(gameboy): W25Q128 flash audio, DTS-driven IRQ, audio API refactor, game/render split
    W25Q128 external flash:
    - SPI3 (PC10/PC11/PC12, CS=PB0) with flash driver
    - Audio streams from flash via dedicated RTOS task
    - Flash upload mode over UART (tools/flash_upload.py)
    - make audio target converts WAV to flash binary
    DTS-driven IRQ binding:
2026-05-22 fix(sim): IPSR/ADDW support + two-pass obstacle rendering
    Sim CPU fixes:
    - Set xPSR IPSR field (bits [8:0]) on interrupt entry
    - Clear IPSR on exception return
    - Add MRS cases for IPSR (sysm=5) and xPSR (sysm=3)
    - Add ADDW/SUBW instruction support (encoding T4)
    Render fix:
